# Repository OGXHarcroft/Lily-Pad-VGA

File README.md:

# Lily Pad VGA

This is a low cost, reasonably easy to assemble VGA, analog audio, and S/PDIF digital audio breakout box for original Xbox. A 1.0-1.4 Xbox console with a VGA patched BIOS is required. VGA mode is not currently supported on 1.6 Xbox consoles. VGA mode is experimental and some displays will not work with a a VGA signal from a Xbox. The embedded video sync separator is intended for SD and ED resolutions. While it may work with 720p and 1080i video modes, they are not recommended or supported.

Multiple BOM files are included and many links for components can be found at the bottom of this page.

### PCB Ordering Details

[Latest Gerbers](https://github.com/OGXHarcroft/Lily-Pad-VGA/releases/latest)
The included gerber files should work with most PCB board houses, but Eagle board files are included if you need to generate new gerbers for your specific board house.

When ordering from JLC PCB the default options are ideal. Board thickness should be 1.6mm.
JLC PCB assembly files are included for all surface mount components. There is a BOM file for the remaining through-hole components aside from the S/PDIF fiber transmitter.

### Part Ordering Information

Additional Materials Required Depending on Your BOM:
- 4x U.FL (aka I-PEX MHF) 2mm diameter terminated coaxial cables at least 15cm long (included in Digikey BOM)
- 4x M3 16mm machine screws (included in Digikey BOM)
- 4x M3xL4xOD4.5mm brass inserts (not included in any BOM)
- 1x Xbox AVIP connector (not included in any BOM)

Optional But Recommended Components:
- GQ-1504 S/PDIF fiber optic transmitter
- the 3D printed case, retention clip, case screws and brass inserts
- XD-08 cable gland for strain relief
- 20-30cm of 4-6mm braided cable sleeving
- Zip-tie for strain relief
- Heat-shrink to make the braided cable sleeving easier to deal with
- Additional wire for strain relief

### Basic Assembly Instructions and Advice

1) Assemble the AVIP connector wire harness with the 4 U.FL terminated coaxial cables and the 5 pin 1.25mm picoblade cable using the image below. The shielding on the cables can be directly soldered to the ground pin for each signal line. An extra piece of wire should be added as extra strain relief to protect the picoblade wires and coaxial cables, and will offer some extra grounding for static discharges.

The added piece of wire can be soldered directly to the shielding of the AVIP connector and to the extra plated through hole on the board to the right of J2, and then through the same sleeving and cable glands as the rest of the wire harness. Ensure this cable is the shortest wire in the harness for proper strain relief. Coloring the U.FL connectors with marker to denote signal they carry may be helpful.

Make sure you put the AVIP connector boot and cable glad onto the wire harness before soldering the wires to the pins on the connector. Adding a small piece of heat shrink on each end of the sleeving will help the sleeving stay in place. Adding a zip tie on the adapter side of the cable gland will help with strain relief.

2) Assemble the PCB with components from the various BOM files and links below. The S/PDIF transmitter (J4) is difficult to find outside of ebay, aliexpress, alibaba etc. Aside from the 3D prints, every component can be purchased from Aliexpress. BOM and CPL files for PCB assembly at JLC PCB for all surface mount components are included in this repo. Trimming the longest legs off the audio and S/PDIF connectors will aid in the best fit for the case. Several BOM files are included in this repo; please read the title of each one carefully for the components you require.

3) Connect the 5 pin cable to J2, connect the Red, Green, Blue, and SPDIF U.FL cables to their corresponding connectors on the VGA adapter board. Insert the retention clip in the holes on either side of the connectors with the slim side pointing up. Melt the pegs that protrude through the back of the PCB to permanently affix the retention clip to the board at 180-200C. Alternatively a twist tie passed through the back of the board can help retain the signal wires.

4) For case assembly, place the smooth end of one of the brass standoffs into each of the 4 holes on the inside of the top half of the case, then melt them into place at a safe temperature for the plastic your case was printed with. Generally 180-200C should be sufficient). After placing the adapter board into the bottom half of the case, make sure to slot the cable glad into the provided slot.

### Links For Components

- Xbox AVIP connector:
https://console5.com/store/microsoft-xbox-av-multi-out-plug-for-custom-rgb-cables-repair-og-original.html
or https://www.aliexpress.com/item/1005005195913174.html
- GQ-1504 S/PDIF transmitter (transmitting): https://www.aliexpress.com/item/1005004654447952.html
- J2 audio connector alternate: https://www.aliexpress.com/item/1005001528210520.html
- M3 16mm screws alternate (6mm): https://www.aliexpress.com/item/1005007188294590.html
- M3xL4xiD4.5mm brass threaded inserts: https://www.aliexpress.com/item/1005006071488810.htm (could not find on digikey)
- DSub15 alternate: https://www.aliexpress.com/item/1005003798059447.html
- DSub15 jackscrew: (outside thread 5mm) https://www.aliexpress.com/item/4000371838126.html
- U.FL terminated coaxial cables: https://www.aliexpress.com/item/1005009463616815.html
- 5 pin 1.25mm picoblade cable: https://www.aliexpress.com/item/1005007277110532.html
- Cable gland (choose XD-08-Black): https://www.aliexpress.com/item/1005005691860036.html 
- Braided cable sleeving: https://www.aliexpress.com/item/1005007486025295.html

### Thanks and Credit

- Kekule for helpful ideas.
- DiscoStarSlayer for helpful advice.
- HoneySoakedSeagull for the frog art.
- Derf for another great project name and GoTeamScotch for contributing to the name.
- Team Cerbios for adding VGA support into their BIOS.

### Attribution

If you modify the board files please do not remove the HCI logo.

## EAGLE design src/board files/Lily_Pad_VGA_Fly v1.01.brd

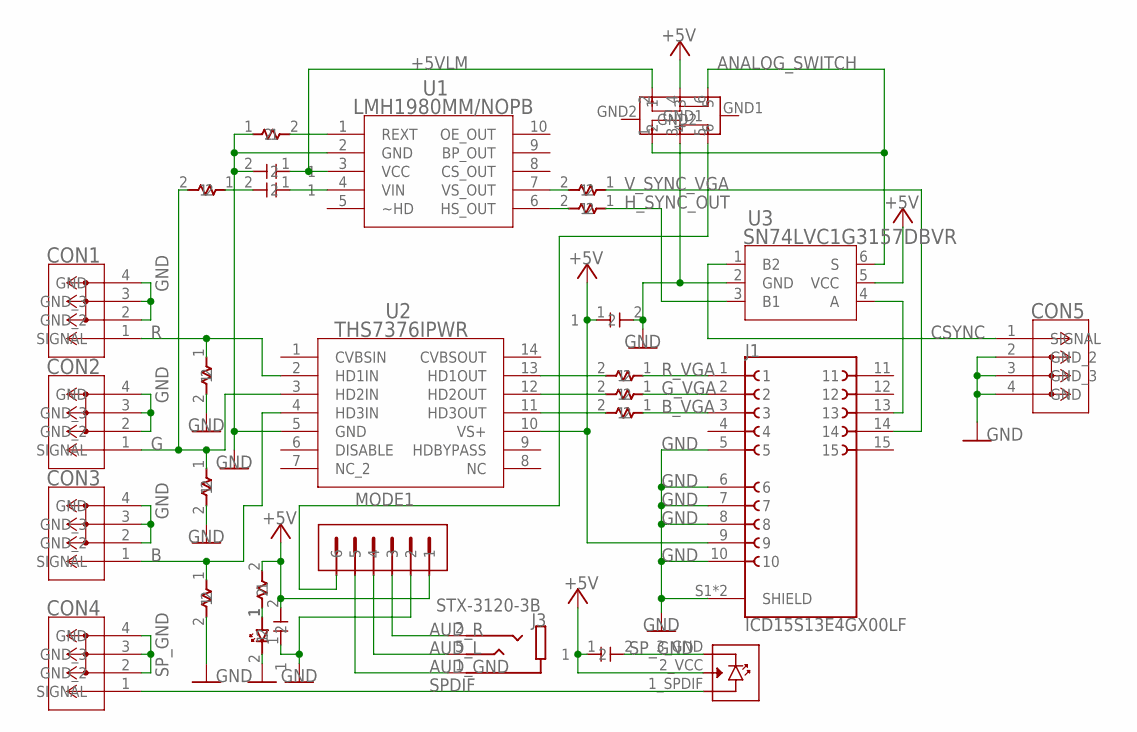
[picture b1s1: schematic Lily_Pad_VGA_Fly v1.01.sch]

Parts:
C1: 22UF; CAPACITOR_SMT_0603
C2, C3, C4, C5: 0.1UF; CAPACITOR_SMT_0603
CON1, CON2, CON3, CON4, CON5: CONMHF1-SMD-G-T; COAX3_CONMHF1-SMD-G-T_TEC
J1: ICD15S13E4GX00LF
J2: 0530470610
J3: STX-3120-3B; KYCON_STX-3120-3B
J4: GQ-1504_OPTICAL
LED1: LED; LED_SMT_0603
R1, R2, R3, R4, R5, R6: 75R; RESISTOR_SMT_0603
R7: 91R; RESISTOR_SMT_0603
R8, R9: 100R; RESISTOR_SMT_0603
RA: 1K; RESISTOR_SMT_0603
RB: 10K; RESISTOR_SMT_0603
SW1: DPDT_SW_SK22D07; DPDT_SK22D07
U1: LMH1980MM/NOPB; MUB10A
U2: THS7376IPWR; PW14_TEX
U3: SN74LVC1G3157DBVR; DBV6

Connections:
+5V: C1.2, C4.1, C5.1, J1.9, J2.1, J4.2_VCC, RA.2, SW1.4, U2.10 (VS+), U3.5 (VCC)
+5VLM: C2.1, SW1.2, U1.3 (VCC)
ANALOG_SWITCH: SW1.1, SW1.6, U3.6 (S)
AUD_GND: J2.5, J3.1
AUD_L: J2.4, J3.5
AUD_R: J2.3, J3.2
B: CON3.1 (SIGNAL), R1.1, U2.4 (HD3IN)
B_OUT: R4.2, U2.11 (HD3OUT)
B_VGA: J1.3, R4.1
CSYNC: CON5.1 (SIGNAL), U3.1 (B2)
G: CON2.1 (SIGNAL), R2.1, R8.2, U2.3 (HD2IN)
GND: C1.1, C2.2, C4.2, CON1.2 (GND_2), CON1.3 (GND_3), CON1.4 (GND), CON2.2 (GND_2), CON2.3 (GND_3), CON2.4 (GND), CON3.2 (GND_2), CON3.3 (GND_3), CON3.4 (GND), CON5.2 (GND_2), CON5.3 (GND_3), CON5.4 (GND), J1.5, J1.6, J1.7, J1.8, J1.10, J1.S1 (SHIELD), J1.S2 (SHIELD), J2.2, LED1.2, R1.2, R2.2, R3.2, RB.1, SW1.3, U1.2 (GND), U2.5 (GND), U3.2 (GND)
G_OUT: R5.2, U2.12 (HD2OUT)
G_SYNC1: C3.2, R8.1
G_SYNC2: C3.1, U1.4 (VIN)
G_VGA: J1.2, R5.1
H_SYNC_OUT: R7.1, U3.3 (B1)
H_SYNC_SPLIT: R7.2, U1.6 (HS_OUT)
H_SYNC_VGA: J1.13, U3.4 (A)
LED: LED1.1, RA.1
MODE1: J2.6, SW1.5
R: CON1.1 (SIGNAL), R3.1, U2.2 (HD1IN)
REF: RB.2, U1.1 (REXT)
R_OUT: R6.2, U2.13 (HD1OUT)
R_VGA: J1.1, R6.1
SPDIF: CON4.1 (SIGNAL), J4.1_SPDIF
SP_GND: C5.2, CON4.2 (GND_2), CON4.3 (GND_3), CON4.4 (GND), J4.3_GND
V_SYNC_SPLIT: R9.2, U1.7 (VS_OUT)
V_SYNC_VGA: J1.14, R9.1

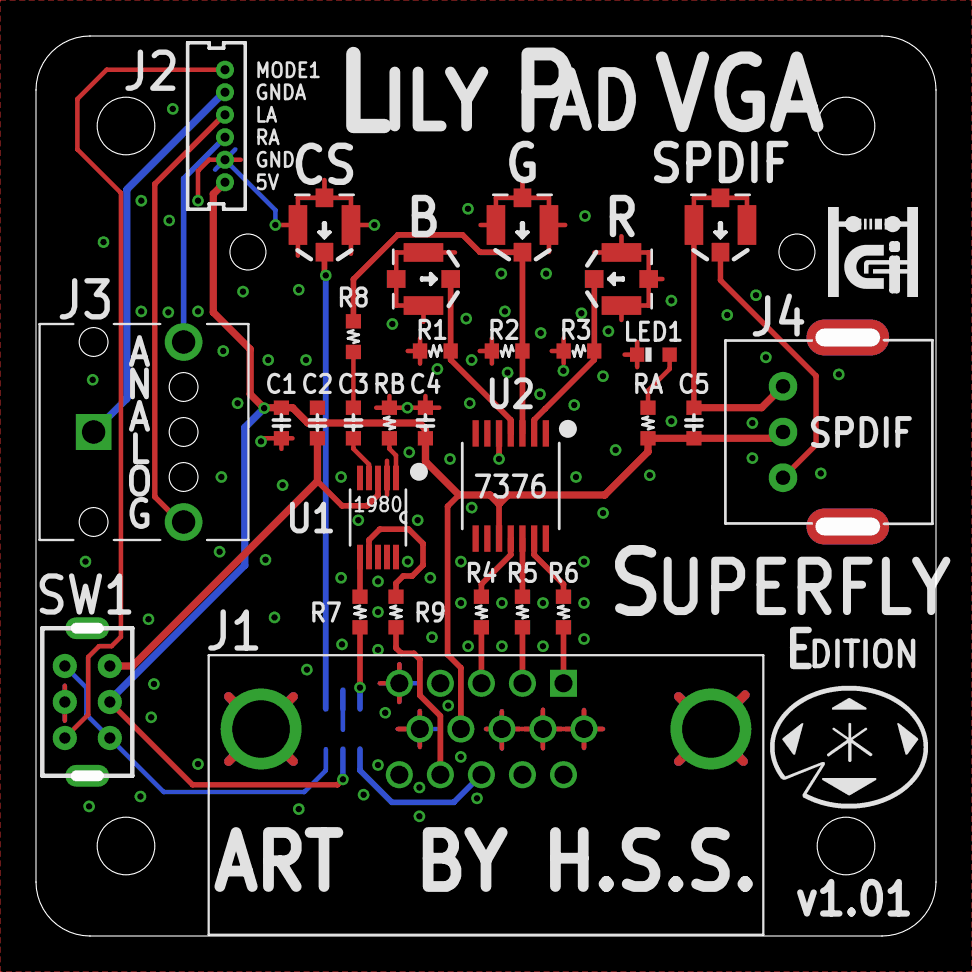
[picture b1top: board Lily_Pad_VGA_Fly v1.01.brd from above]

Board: 2 copper layers, 49.0 x 49.0 mm, 31 parts (1 on the bottom side), 29 nets.

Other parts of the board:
U$2: HCI_LOGO_5MM

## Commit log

2026-01-31 Formatting corrections and 3D models added
2026-01-31 Corrected releases link
2026-01-31 corrected typo
    M3xL4xOD4.5mm brass threaded inserts
2026-01-31 More cleanup of readme
2026-01-31 added intents for paragraphs on step 1 of assembly
2026-01-31 Update README.md
    more spelling corrections and additional credit

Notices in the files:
parts and their libraries:
COPYRIGHT: Copyright (C) 2024 Ultra Librarian. All rights reserved.
COPYRIGHT: Copyright (C) 2025 Ultra Librarian. All rights reserved.
